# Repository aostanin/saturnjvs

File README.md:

# SaturnJVS

A project to build a replacement JVS I/O board for a NAOMI arcade board which uses Sega Saturn controllers as input.

## Details

This relies on two boards which communicate by I2C. One board handles JVS communication with the NAOMI while the other handles controller input from Sega Saturn controllers. Originally, the plan was to support different types of controllers by swapping controller input boards.

Both boards rely on Atmel AVR ATmega328P microcontrollers and the firmware is written using the Arduino framework. The boards, however, are custom made and not arduino boards (though Arduino boards might be usable as well).

## Status

Using standard Sega Saturn controllers to play games on a NAOMI 2 board works well. There are some missing features including analog pad support and button remapping.

This project is on hold.

## Directory Layout

- `eagle`: Eagle schematics and board layout data.
- `naomi_io`: Firmware for the JVS communication board.
- `saturn_js`: Firmware for the Sega Saturn controller board.

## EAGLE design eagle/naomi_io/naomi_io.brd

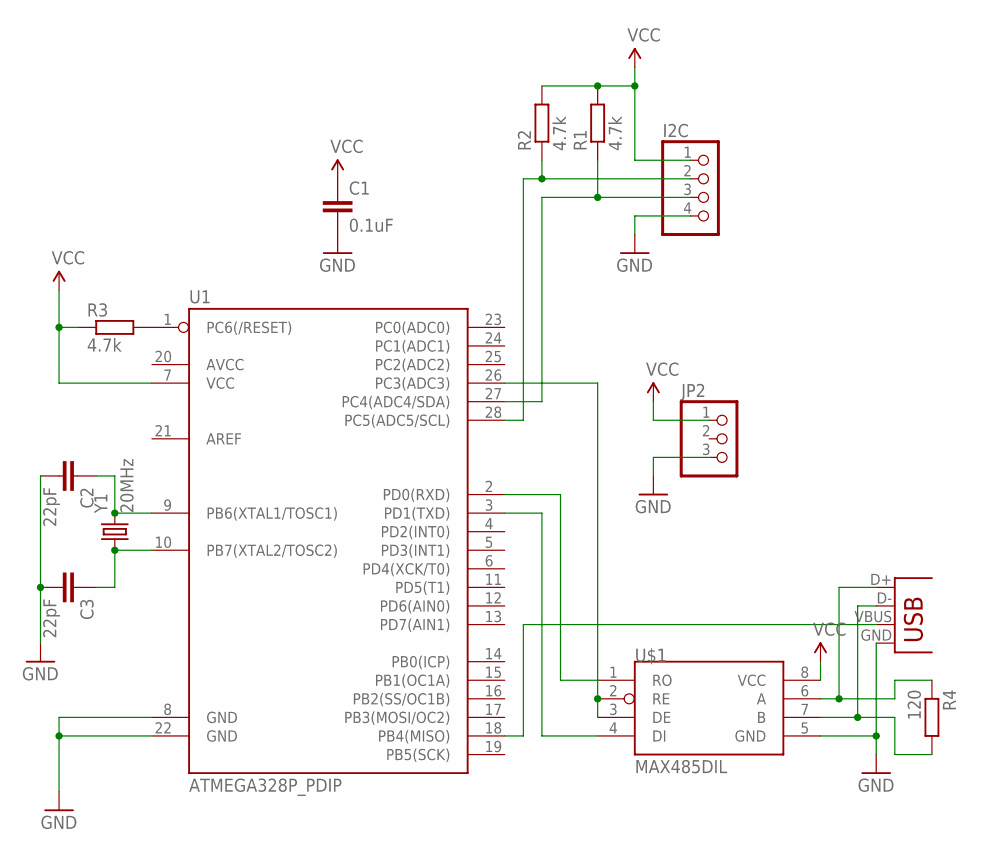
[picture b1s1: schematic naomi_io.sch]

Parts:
C1: 0.1uF; C025-030X050
C2, C3: 22pF; C025-030X050
I2C: PINHD-1X4/90; 1X04/90
JP1: USB-B; USB-B-PTH
JP2: PINHD-1X3; 1X03
R1, R2, R3: 4.7k; 0204/5
R4: 120; 0204/5
U1: ATMEGA328P_PDIP; DIL28-3
U$1: MAX485DIL; DIL08
Y1: 20MHz; HC49US

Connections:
GND: C1.2, C2.2, C3.2, I2C.4, JP1.GND, JP2.3, U1.8 (GND), U1.22 (GND), U$1.5 (GND)
unnamed: I2C.2, R2.1, U1.28 (PC5(ADC5/SCL))
unnamed: I2C.3, R1.1, U1.27 (PC4(ADC4/SDA))
unnamed: R3.2, U1.1 (PC6(/RESET))
unnamed: JP1.D-, R4.2, U$1.7 (B)
unnamed: U1.2 (PD0(RXD)), U$1.1 (RO)
unnamed: U1.3 (PD1(TXD)), U$1.4 (DI)
unnamed: JP1.VBUS, U1.18 (PB4(MISO))
unnamed: U1.26 (PC3(ADC3)), U$1.2 (RE), U$1.3 (DE)
unnamed: C2.1, U1.9 (PB6(XTAL1/TOSC1)), Y1.2
unnamed: C3.1, U1.10 (PB7(XTAL2/TOSC2)), Y1.1
unnamed: JP1.D+, R4.1, U$1.6 (A)
VCC: C1.1, I2C.1, JP2.1, R1.2, R2.2, R3.1, U1.7 (VCC), U$1.8 (VCC)

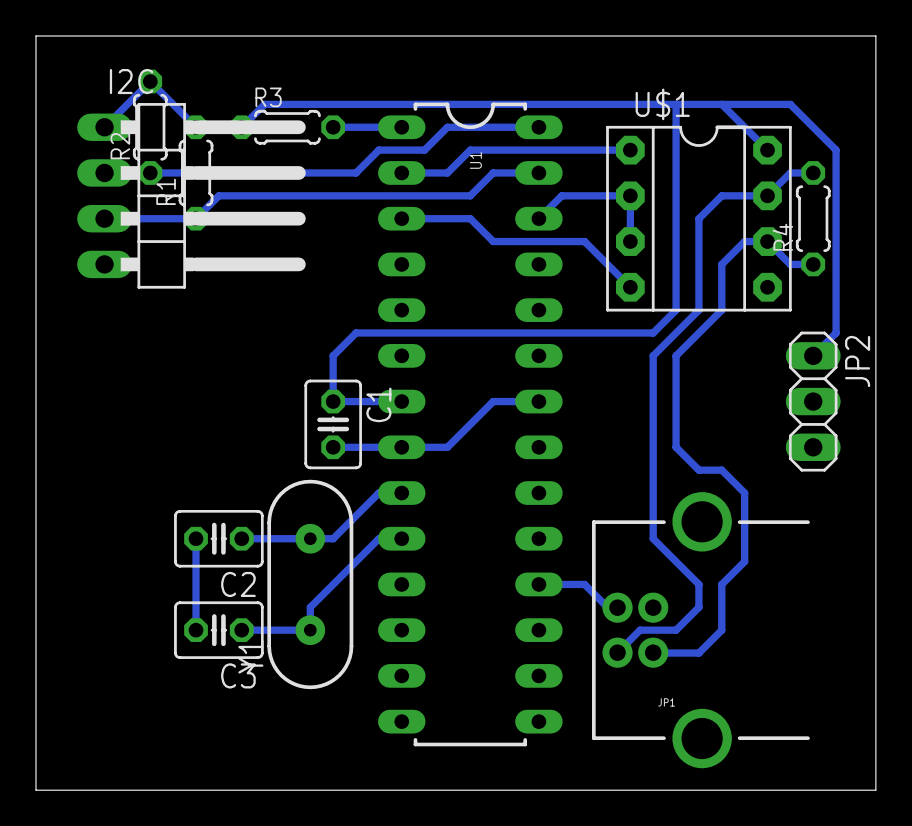
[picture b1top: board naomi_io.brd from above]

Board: 2 copper layers, 46.7 x 41.9 mm, 13 parts (0 on the bottom side), 13 nets.

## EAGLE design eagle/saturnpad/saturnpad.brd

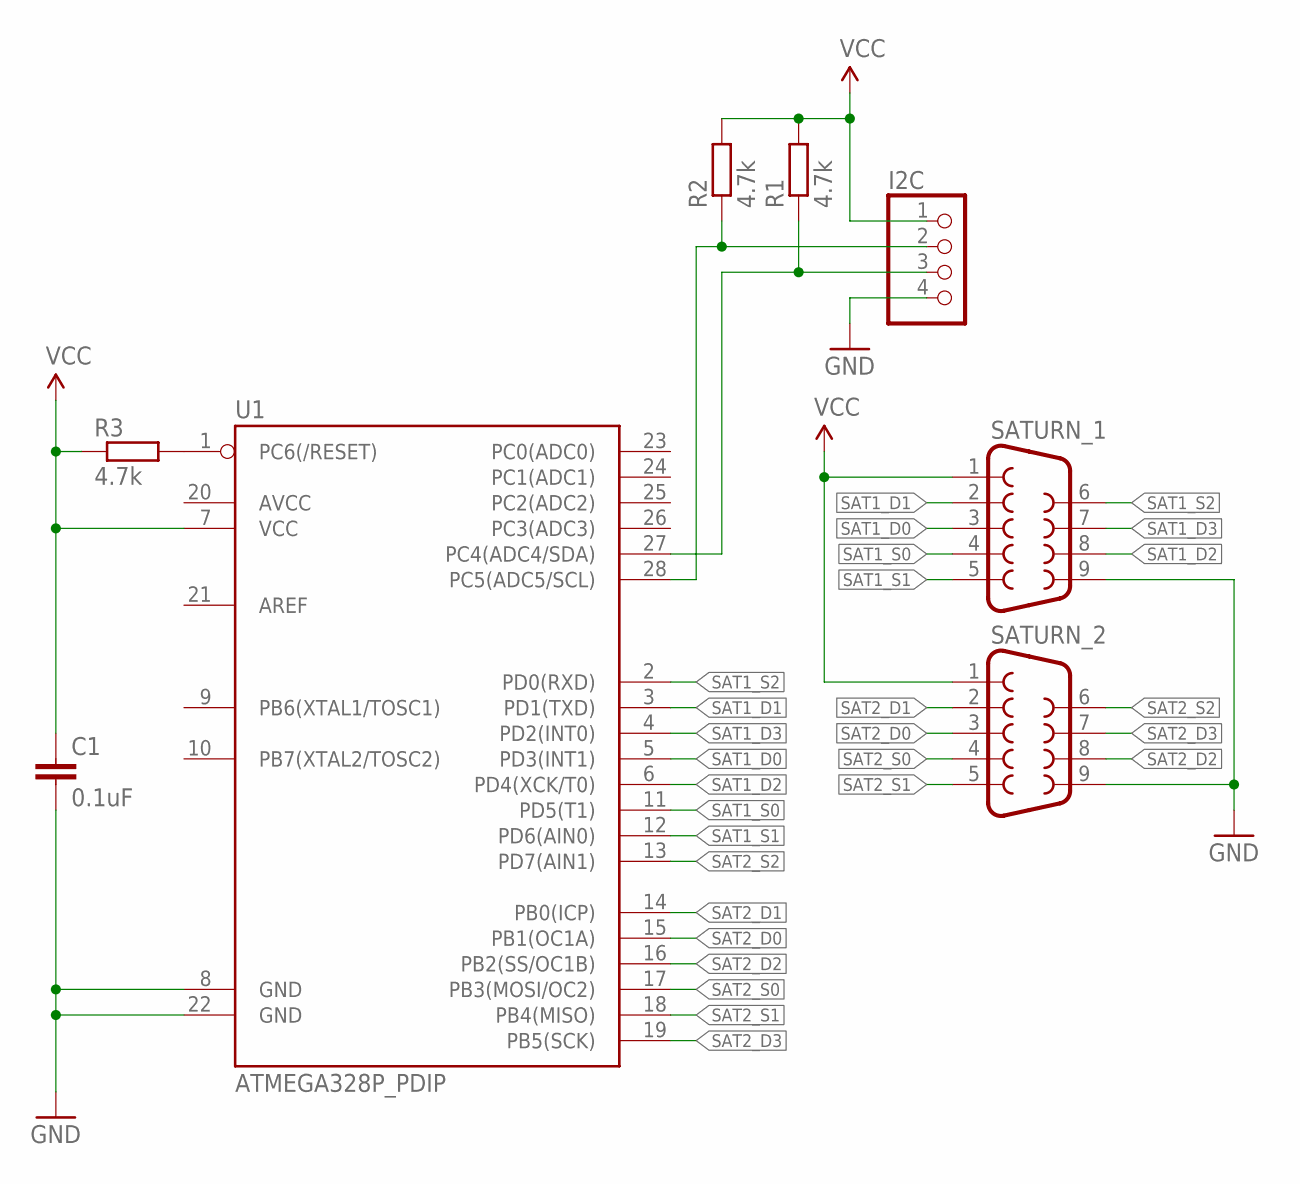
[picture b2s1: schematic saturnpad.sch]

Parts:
C1: 0.1uF; C025-030X050
I2C: PINHD-1X4/90; 1X04/90
R1, R2, R3: 4.7k; 0204/5
SATURN_1, SATURN_2: DB9MALE; DB9_MALE
U1: ATMEGA328P_PDIP; DIL28-3

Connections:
GND: C1.2, I2C.4, SATURN_1.9, SATURN_2.9, U1.8 (GND), U1.22 (GND)
unnamed: I2C.2, R2.1, U1.28 (PC5(ADC5/SCL))
unnamed: I2C.3, R1.1, U1.27 (PC4(ADC4/SDA))
unnamed: R3.2, U1.1 (PC6(/RESET))
SAT1_D0: SATURN_1.3, U1.5 (PD3(INT1))
SAT1_D1: SATURN_1.2, U1.3 (PD1(TXD))
SAT1_D2: SATURN_1.8, U1.6 (PD4(XCK/T0))
SAT1_D3: SATURN_1.7, U1.4 (PD2(INT0))
SAT1_S0: SATURN_1.4, U1.11 (PD5(T1))
SAT1_S1: SATURN_1.5, U1.12 (PD6(AIN0))
SAT1_S2: SATURN_1.6, U1.2 (PD0(RXD))
SAT2_D0: SATURN_2.3, U1.15 (PB1(OC1A))
SAT2_D1: SATURN_2.2, U1.14 (PB0(ICP))
SAT2_D2: SATURN_2.8, U1.16 (PB2(SS/OC1B))
SAT2_D3: SATURN_2.7, U1.19 (PB5(SCK))
SAT2_S0: SATURN_2.4, U1.17 (PB3(MOSI/OC2))
SAT2_S1: SATURN_2.5, U1.18 (PB4(MISO))
SAT2_S2: SATURN_2.6, U1.13 (PD7(AIN1))
VCC: C1.1, I2C.1, R1.2, R2.2, R3.1, SATURN_1.1, SATURN_2.1, U1.7 (VCC)

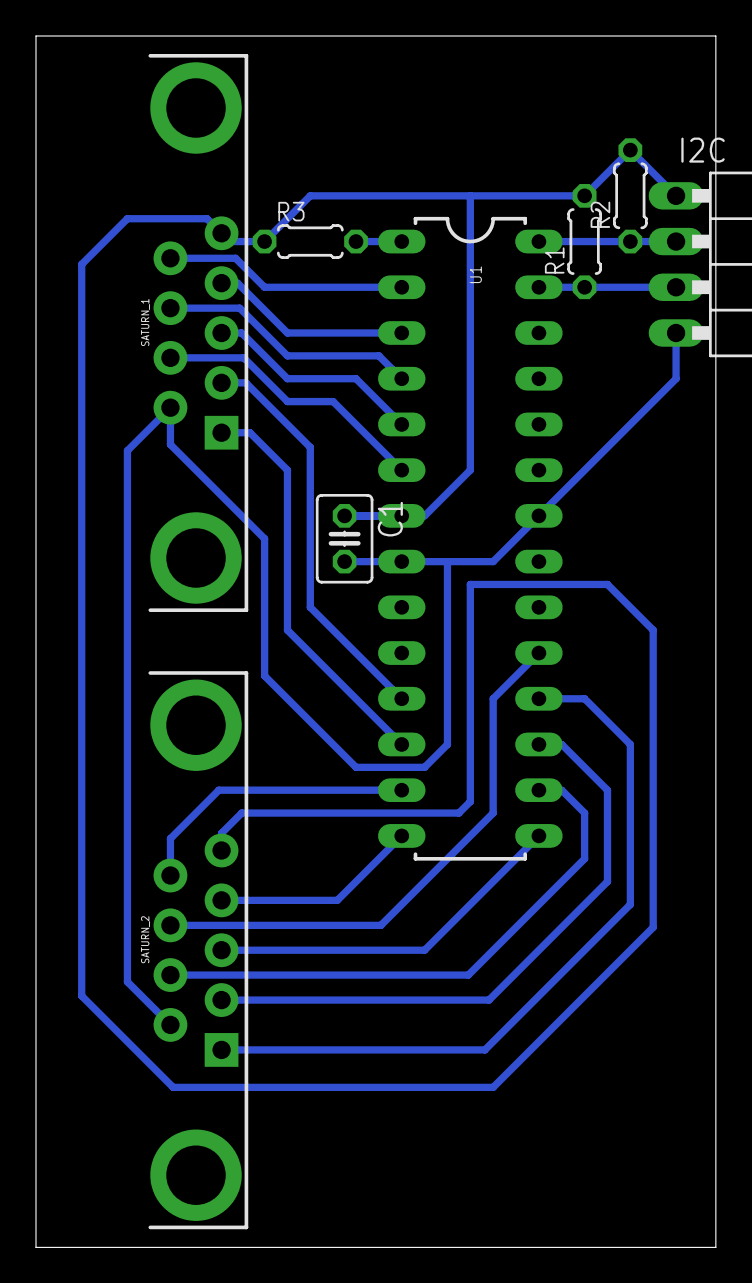
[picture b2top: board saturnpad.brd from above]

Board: 2 copper layers, 37.8 x 67.3 mm, 8 parts (0 on the bottom side), 19 nets.

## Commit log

2014-05-26 Remove debug code and fix runtime problem on AVR
2014-05-26 add support for third select line for eventual analog support
2014-05-26 fix pin numbers for final board
2014-05-27 Add rotary switch support
2014-08-21 Oops... JVS expects the top row of buttons to be 1 2 3 and bottom to be 4 5 6
2016-02-21 add fuses config
2016-02-21 add eagle files
2016-02-21 add README

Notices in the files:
parts and their libraries:
SparkFun-DigitalIC: Licensing: Creative Commons ShareAlike 4.0 International - https://creativecommons.org/licenses/by-sa/4.0
